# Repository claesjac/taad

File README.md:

taad
====

Tiny Autonomous Aerial Drone

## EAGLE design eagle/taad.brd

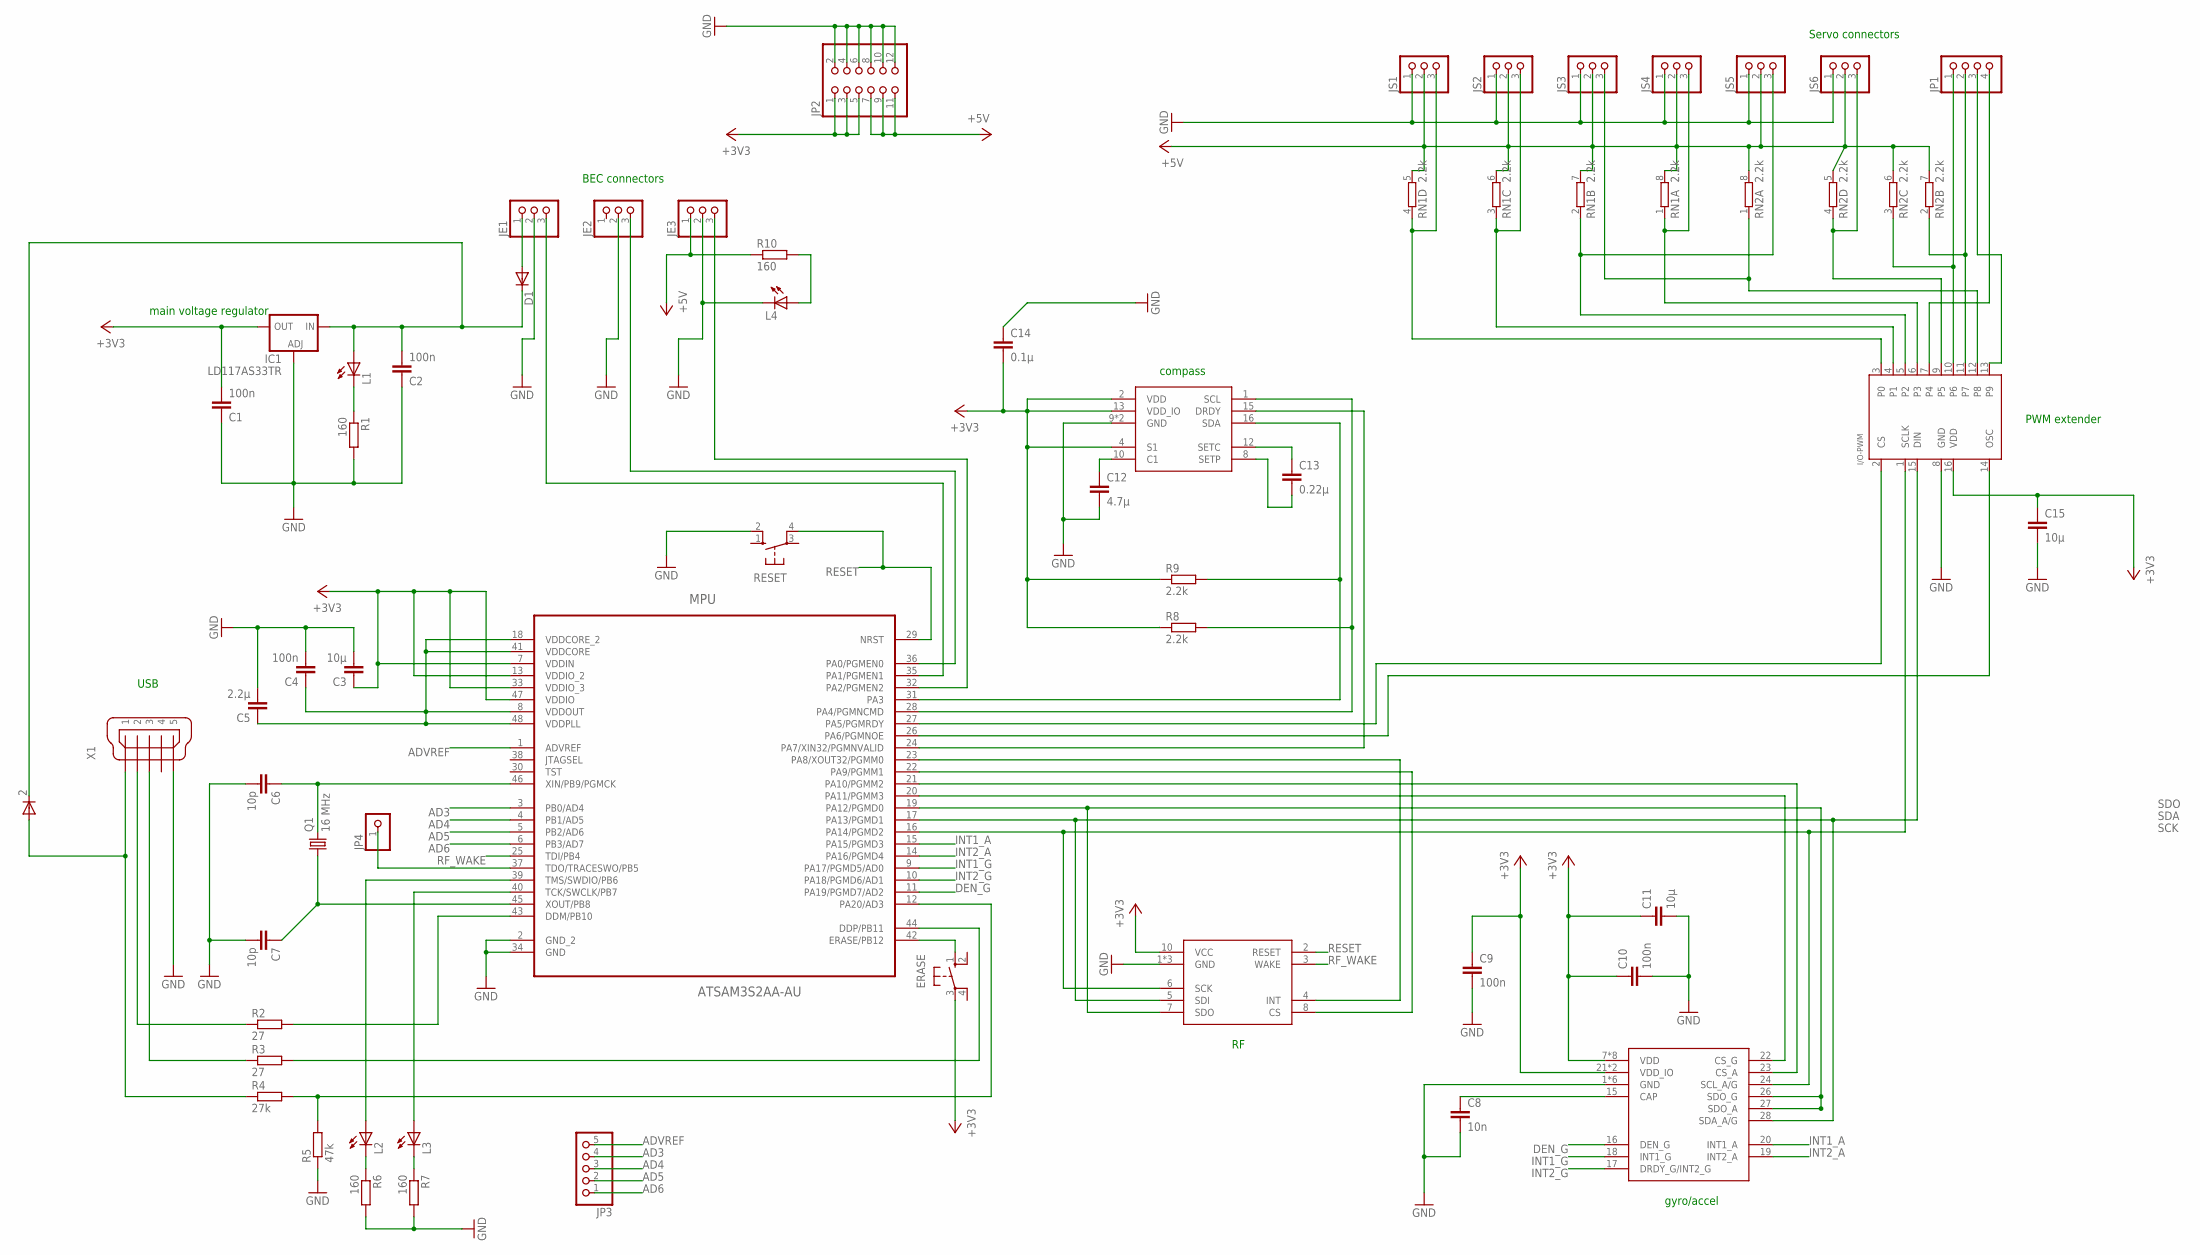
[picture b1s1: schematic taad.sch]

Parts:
2: DIODE-SOD123; SOD123
C1, C2, C4, C9, C10: 100n; C0805
C3, C11, C15: 10µ; C0805
C5: 2.2µ; C0805
C6, C7: 10p; C0805
C8: 10n; C0805
C12: 4.7µ; C0805
C13: 0.22µ; C0805
C14: 0.1µ; C0805
COMPASS: HMC5883L; LPCC16
D1: DIODE-SOD123; SOD123
ERASE: 10-XX; B3F-10XX
GYRO/ACCEL: LSM330DLC; LGA-28L
I/O-PWM: MAX6967AEE; QSOP16
IC1: LD117AS33TR; SOT223
JE1, JE2, JE3: PINHD-1X3; 1X03
JP1: PINHD-1X4; 1X04
JP2: PINHD-2X6; 2X06
JP3: PINHD-1X5; 1X05
JP4: PINHD-1X1; 1X01
JS1, JS2, JS3, JS4, JS5, JS6: PINHD-1X3; 1X03
L1, L2, L3, L4: LEDCHIP-LED0805; CHIP-LED0805
MPU: ATSAM3S2AA-AU; QFP50P900X900X160-48N
Q1: 16 MHz; HC49UP
R1, R6, R7, R10: 160; R0805
R2, R3: 27; R0805
R4: 27k; R0805
R5: 47k; R0805
R8, R9: 2.2k; R0805
RESET: 10-XX; B3F-10XX
RF: MRF24J40MA_TRANSEIVER_MODULE; PIN_HEADERS
RN1, RN2: 2.2k; EXB38V
X1: MINI-USB-32005-201; 32005-201

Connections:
+3V3: C1.2, C3.1, C9.1, C10.1, C11.1, C14.2, C15.1, COMPASS.2 (VDD), COMPASS.4 (S1), COMPASS.13 (VDD_IO), ERASE.3, GYRO/ACCEL.7 (VDD), GYRO/ACCEL.8 (VDD), GYRO/ACCEL.9 (VDD), GYRO/ACCEL.10 (VDD), GYRO/ACCEL.11 (VDD), GYRO/ACCEL.12 (VDD), GYRO/ACCEL.13 (VDD), GYRO/ACCEL.14 (VDD), GYRO/ACCEL.21 (VDD_IO), GYRO/ACCEL.25 (VDD_IO), I/O-PWM.16 (VDD), IC1.4 (OUT), JP2.1, JP2.3, JP2.5, MPU.7 (VDDIN), MPU.13 (VDDIO_2), MPU.33 (VDDIO_3), MPU.47 (VDDIO), R8.1, R9.1, RF.10 (VCC)
+5V: JE3.1, JP2.7, JP2.9, JP2.11, JS1.2, JS2.2, JS3.2, JS4.2, JS5.2, JS6.2, R10.1, RN1.5 (2), RN1.6 (2), RN1.7 (2), RN1.8 (2), RN2.5 (2), RN2.6 (2), RN2.7 (2), RN2.8 (2)
AD3: JP3.4, MPU.3 (PB0/AD4)
AD4: JP3.3, MPU.4 (PB1/AD5)
AD5: JP3.2, MPU.5 (PB2/AD6)
AD6: JP3.1, MPU.6 (PB3/AD7)
ADVREF: JP3.5, MPU.1 (ADVREF)
COMPASS_DATA_READY: COMPASS.15 (DRDY), MPU.24 (PA7/XIN32/PGMNVALID)
DDM: MPU.43 (DDM/PB10), R2.2
DDP: MPU.44 (DDP/PB11), R3.2
DEN_G: GYRO/ACCEL.16 (DEN_G), MPU.11 (PA19/PGMD7/AD2)
ESC1: JE1.3, MPU.35 (PA1/PGMEN1)
ESC2: JE2.3, MPU.36 (PA0/PGMEN0)
ESC3: JE3.3, MPU.32 (PA2/PGMEN2)
GND: C1.1, C2.1, C3.2, C4.2, C5.2, C6.2, C7.2, C8.2, C9.2, C10.2, C11.2, C12.2, C14.1, C15.2, COMPASS.9 (GND), COMPASS.11 (GND), GYRO/ACCEL.1 (GND), GYRO/ACCEL.2 (GND), GYRO/ACCEL.3 (GND), GYRO/ACCEL.4 (GND), GYRO/ACCEL.5 (GND), GYRO/ACCEL.6 (GND), I/O-PWM.8 (GND), IC1.1 (ADJ), JE1.2, JE2.2, JE3.2, JP2.2, JP2.4, JP2.6, JP2.8, JP2.10, JP2.12, JS1.1, JS2.1, JS3.1, JS4.1, JS5.1, JS6.1, L4.C, MPU.2 (GND_2), MPU.34 (GND), R1.2, R5.1, R6.2, R7.2, RESET.2 (S1), RF.1 (GND), RF.11 (GND), RF.12 (GND), X1.5
INT1_A: GYRO/ACCEL.20 (INT1_A), MPU.15 (PA15/PGMD3)
INT1_G: GYRO/ACCEL.18 (INT1_G), MPU.9 (PA17/PGMD5/AD0)
INT2_A: GYRO/ACCEL.19 (INT2_A), MPU.14 (PA16/PGMD4)
INT2_G: GYRO/ACCEL.17 (DRDY_G/INT2_G), MPU.10 (PA18/PGMD6/AD1)
IO1: I/O-PWM.10 (P6), JP1.1, RN2.3 (1)
IO2: I/O-PWM.11 (P7), JP1.2, RN2.2 (1)
IO3: I/O-PWM.13 (P9), JP1.3
IO4: I/O-PWM.7 (P4), JP1.4
unnamed: D1.A, JE1.1
unnamed: L2.A, MPU.39 (TMS/SWDIO/PB6)
unnamed: R3.1, X1.3
unnamed: R2.1, X1.2
unnamed: L1.C, R1.1
unnamed: L3.A, MPU.40 (TCK/SWCLK/PB7)
unnamed: L4.A, R10.2
unnamed: L2.C, R6.1
unnamed: L3.C, R7.1
unnamed: ERASE.1 (S), MPU.42 (ERASE/PB12)
unnamed: JP4.1, MPU.37 (TDO/TRACESWO/PB5)
unnamed: 2.C, C2.2, D1.C, IC1.3 (IN), L1.A
unnamed: C13.2, COMPASS.8 (SETP)
unnamed: C13.1, COMPASS.12 (SETC)
unnamed: C12.1, COMPASS.10 (C1)
unnamed: C8.1, GYRO/ACCEL.15 (CAP)
NPCS0: GYRO/ACCEL.22 (CS_G), MPU.20 (PA11/PGMM3)
NPCS1: MPU.22 (PA9/PGMM1), RF.8 (CS)
NPCS2: GYRO/ACCEL.23 (CS_A), MPU.21 (PA10/PGMM2)
NPCS3: I/O-PWM.2 (CS), MPU.27 (PA5/PGMRDY)
PWM_CLOCK: I/O-PWM.14 (OSC), MPU.26 (PA6/PGMNOE)
RESET: MPU.29 (NRST), RESET.4 (P1), RF.2 (RESET)
RF_INT: MPU.23 (PA8/XOUT32/PGMM0), RF.4 (INT)
RF_WAKE: MPU.25 (TDI/PB4), RF.3 (WAKE)
SCK: GYRO/ACCEL.24 (SCL_A/G), I/O-PWM.1 (SCLK), MPU.16 (PA14/PGMD2), RF.6 (SCK)
SDA: GYRO/ACCEL.28 (SDA_A/G), I/O-PWM.15 (DIN), MPU.17 (PA13/PGMD1), RF.5 (SDI)
SDO: GYRO/ACCEL.26 (SDO_G), GYRO/ACCEL.27 (SDO_A), MPU.19 (PA12/PGMD0), RF.7 (SDO)
SRV1: I/O-PWM.3 (P0), JS1.3, RN1.4 (1)
SRV2: I/O-PWM.4 (P1), JS2.3, RN1.3 (1)
SRV3: I/O-PWM.5 (P2), JS5.3, RN1.2 (1)
SRV4: I/O-PWM.6 (P3), JS4.3, RN1.1
SRV5: I/O-PWM.12 (P8), JS3.3, RN2.1
SRV6: I/O-PWM.9 (P5), JS6.3, RN2.4 (1)
TWI_CLOCK: COMPASS.1 (SCL), MPU.28 (PA4/PGMNCMD), R8.2
TWI_DATA: COMPASS.16 (SDA), MPU.31 (PA3), R9.2
USB+5V: 2.A, R4.1, X1.1
USB_CONNECTED: MPU.12 (PA20/AD3), R4.2, R5.2
VDDCORE: C4.1, C5.1, MPU.8 (VDDOUT), MPU.18 (VDDCORE_2), MPU.41 (VDDCORE), MPU.48 (VDDPLL)
XIN: C6.1, MPU.46 (XIN/PB9/PGMCK), Q1.2
XOUT: C7.1, MPU.45 (XOUT/PB8), Q1.1

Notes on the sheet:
compass
gyro/accel
PWM extender
main voltage regulator
BEC connectors
Servo connectors
USB

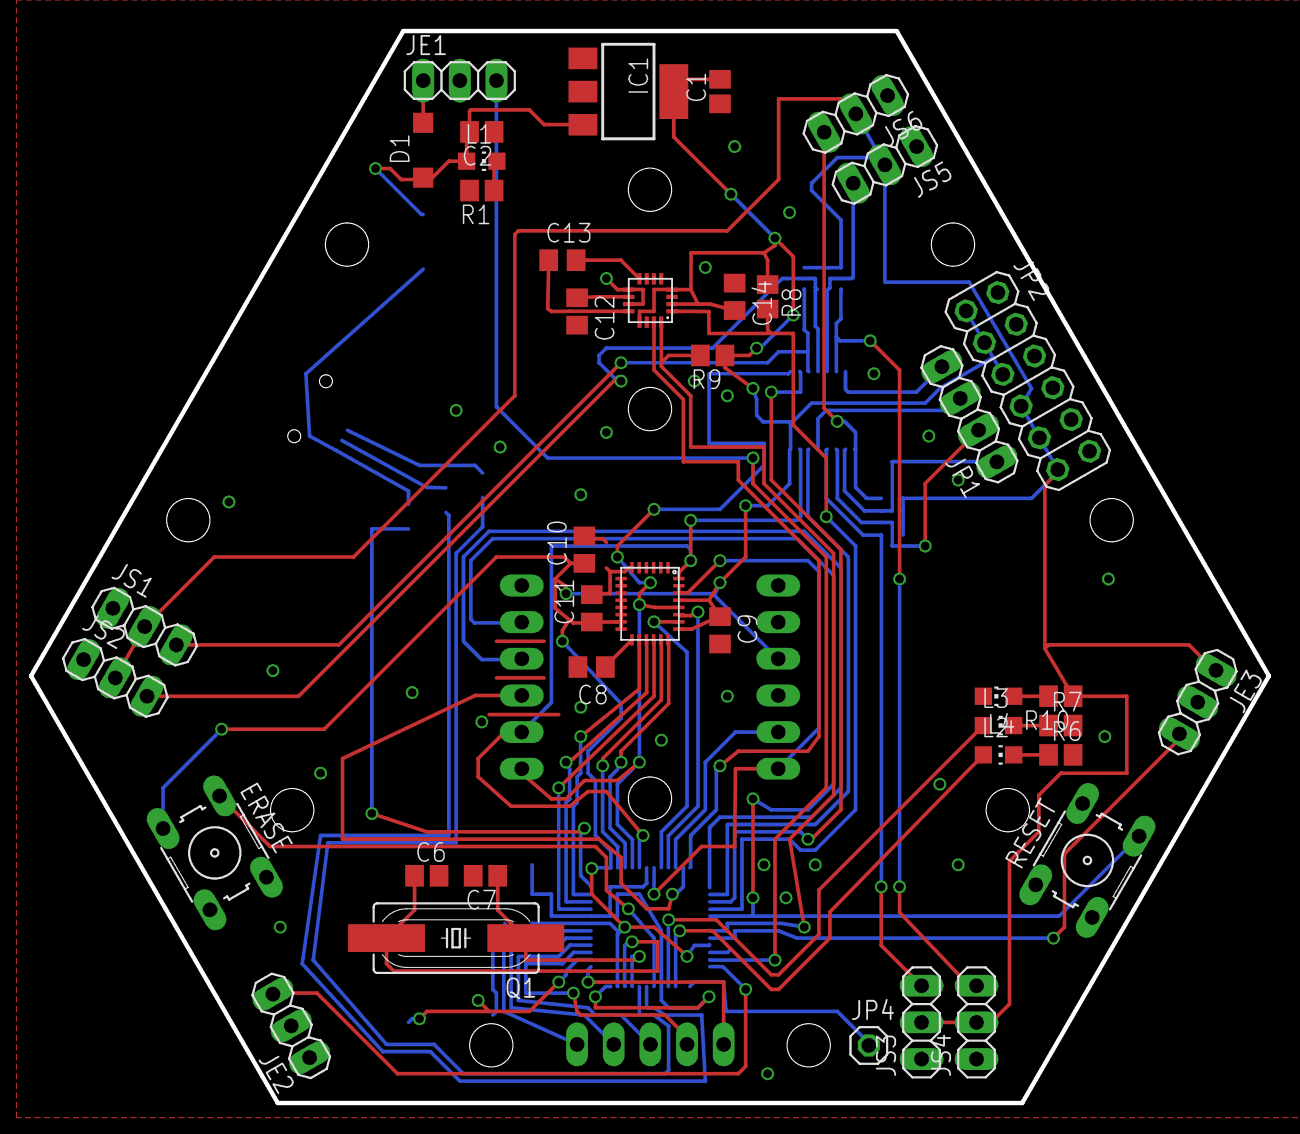
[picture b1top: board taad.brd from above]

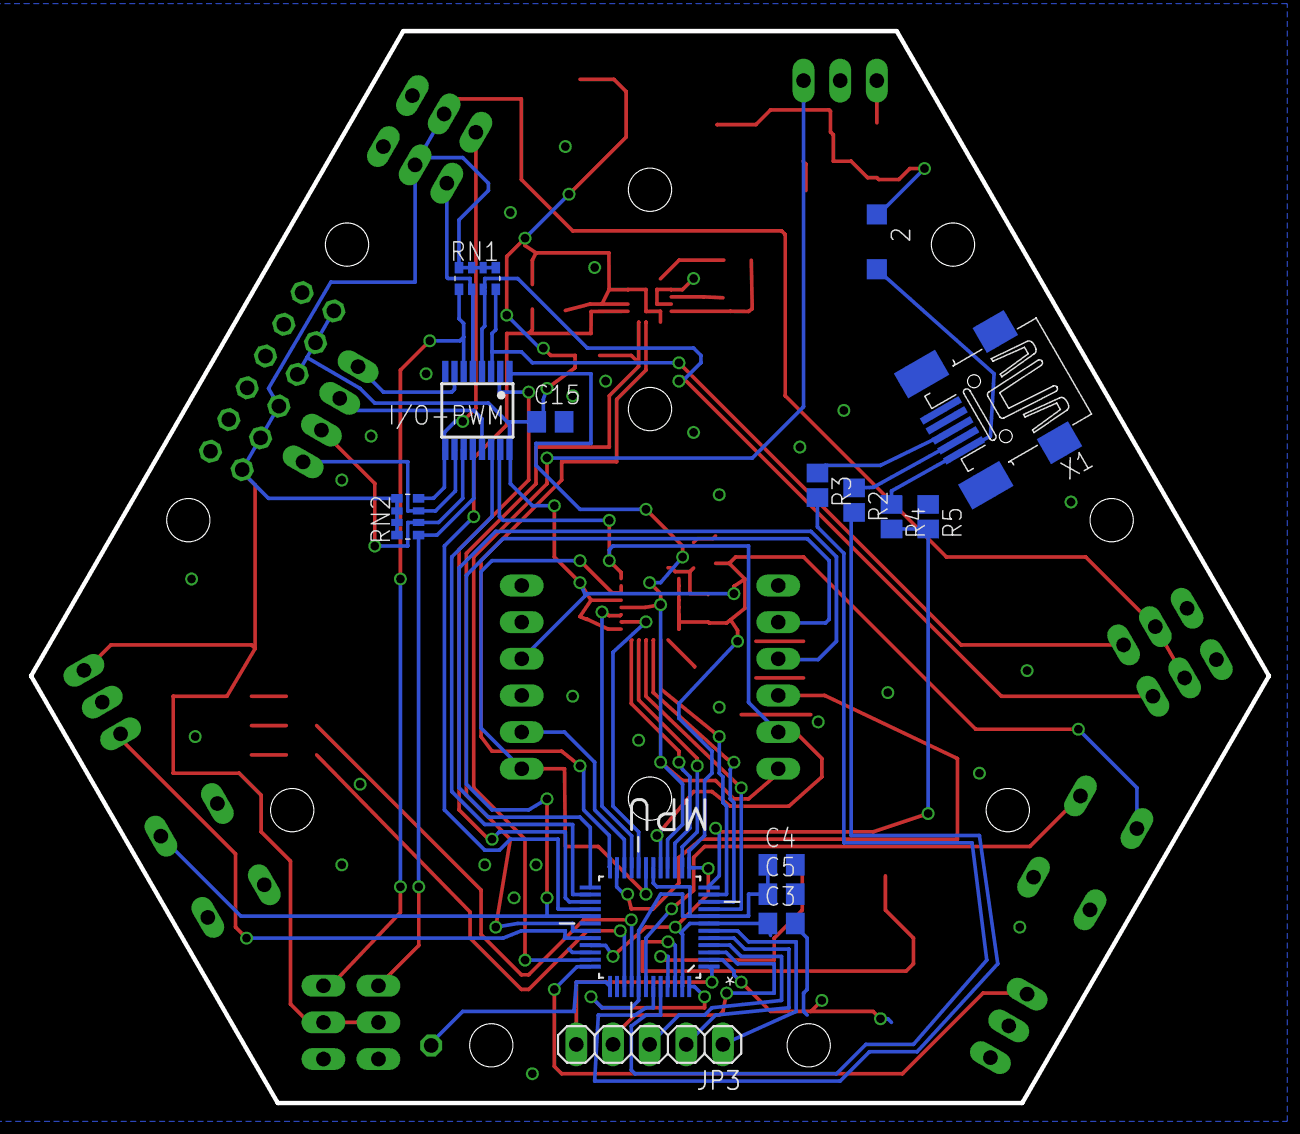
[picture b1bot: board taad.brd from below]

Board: 2 copper layers, 85.8 x 74.3 mm, 56 parts (15 on the bottom side), 63 nets.

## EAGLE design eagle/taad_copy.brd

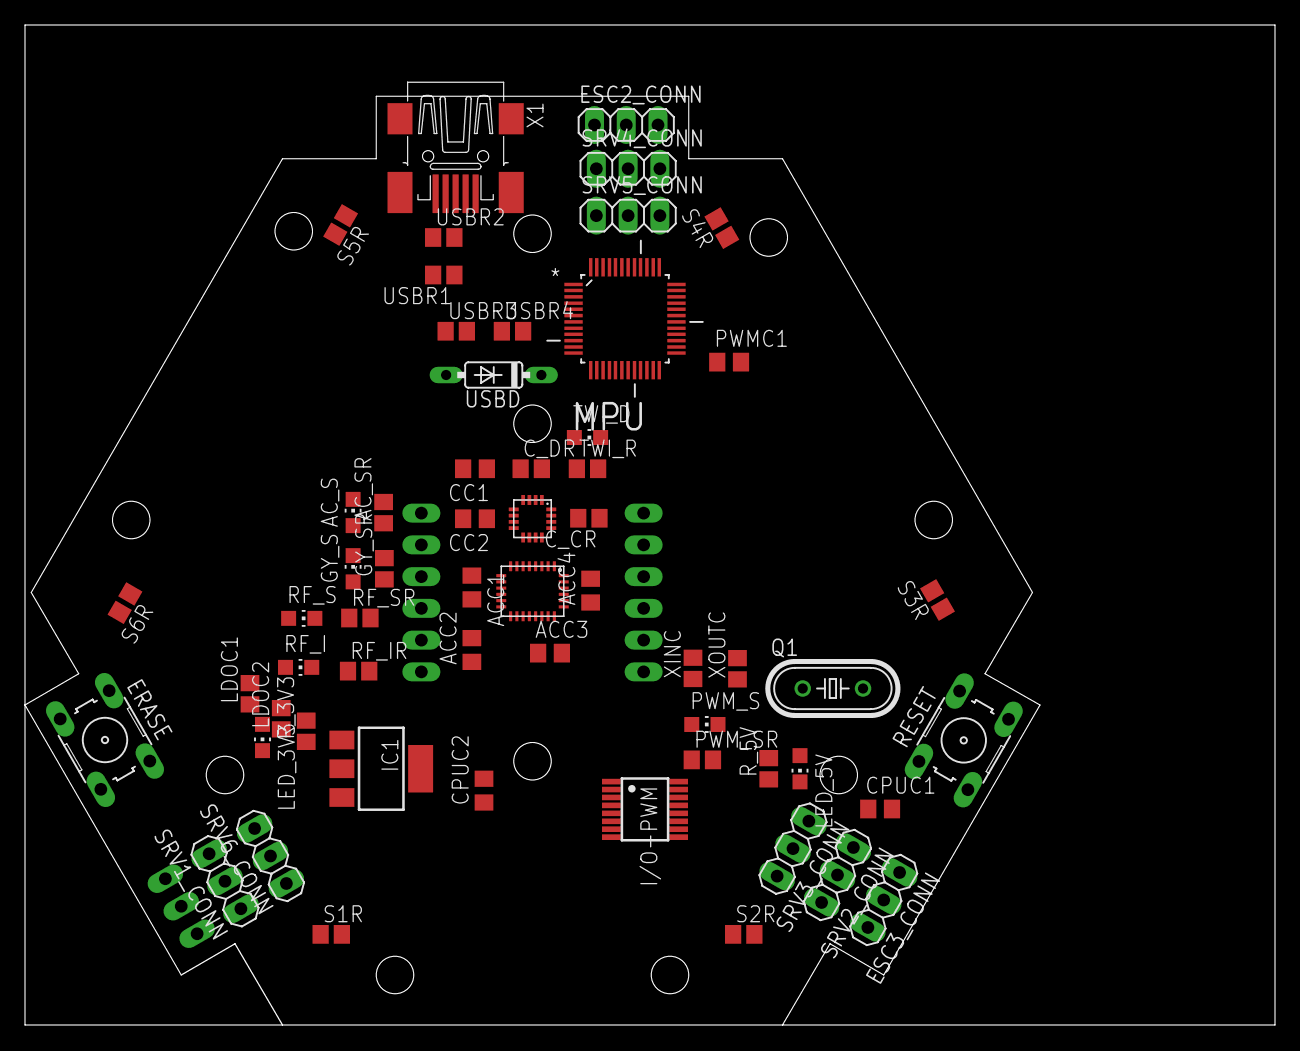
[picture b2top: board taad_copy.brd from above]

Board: 2 copper layers, 99.9 x 80.0 mm, 61 parts (1 on the bottom side), 54 nets, no tracks yet.

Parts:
ACC1, ACC3: 100n; C0805
ACC2: 10µ; C0805
ACC4: 10n; C0805
AC_S: CHIP-LED0805
AC_SR: 2.2k; R0805
CC1: 0.22µ; C0805
CC2: 4.7µ; C0805
COMPASS: HMC5883L; LPCC16
CPUC1: 2.2µ; C0805
CPUC2: 10µ; C0805
C_CR: 2.2k; R0805
C_DR: 2.2k; R0805
ERASE: B3F-10XX
ESC1_CONN, ESC2_CONN, ESC3_CONN: 1X03
GYRO/ACCEL: LSM330DLC; LGA-28L
GY_S: CHIP-LED0805
GY_SR: 2.2k; R0805
I/O-PWM: QSOP16
IC1: LD117AS33TR; SOT223
LDOC1, LDOC2: 100n; C0805
LED_3V3, LED_5V: CHIP-LED0805
MPU: ATSAM3S2AA-AU; QFP50P900X900X160-48N
PWMC1: 10µ; C0805
PWM_S: CHIP-LED0805
PWM_SR: 2.2k; R0805
Q1: 16 MHz; HC49/S
RESET: B3F-10XX
RF: MRF24J40MA_TRANSEIVER_MODULE; PIN_HEADERS
RF_I: CHIP-LED0805
RF_IR: 2.2k; R0805
RF_S: CHIP-LED0805
RF_SR: 2.2k; R0805
R_3V3, R_5V: 160; R0805
S1R, S2R, S3R, S4R, S5R, S6R: 2.2k; R0805
SRV1_CONN, SRV2_CONN, SRV3_CONN, SRV4_CONN, SRV5_CONN, SRV6_CONN: 1X03
TWI_D: CHIP-LED0805
TWI_R: 2.2k; R0805
USBD: 1N4148DO35-7; DO35-7
USBR1, USBR2: 27; R0805
USBR3: 27k; R0805
USBR4: 47k; R0805
X1: MINI-USB-32005-201; 32005-201
XINC: 10p; C0805
XOUTC: 10p; C0805

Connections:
+3V3: ACC1.1, ACC2.1, ACC3.1, COMPASS.2, COMPASS.4, COMPASS.13, CPUC2.1, C_CR.1, C_DR.1, ERASE.3, GYRO/ACCEL.7, GYRO/ACCEL.8, GYRO/ACCEL.9, GYRO/ACCEL.10, GYRO/ACCEL.11, GYRO/ACCEL.12, GYRO/ACCEL.13, GYRO/ACCEL.14, GYRO/ACCEL.21, GYRO/ACCEL.25, I/O-PWM.16, IC1.4, LDOC2.2, MPU.7, MPU.13, MPU.33, MPU.47, PWMC1.1, RF.10
+5V: ESC3_CONN.1, R_5V.1, S1R.2, S2R.2, S3R.2, S4R.2, S5R.2, S6R.2, SRV1_CONN.2, SRV2_CONN.2, SRV3_CONN.2, SRV4_CONN.2, SRV5_CONN.2, SRV6_CONN.2
DEN_G: GYRO/ACCEL.16, MPU.9
ESC1: ESC1_CONN.3, MPU.36
ESC2: ESC2_CONN.3, MPU.35
ESC3: ESC3_CONN.3, MPU.32
GND: ACC1.2, ACC2.2, ACC3.2, ACC4.2, AC_S.C, CC2.2, COMPASS.9, COMPASS.11, CPUC1.2, CPUC2.2, ESC1_CONN.2, ESC2_CONN.2, ESC3_CONN.2, GYRO/ACCEL.1, GYRO/ACCEL.2, GYRO/ACCEL.3, GYRO/ACCEL.4, GYRO/ACCEL.5, GYRO/ACCEL.6, GY_S.C, I/O-PWM.8, IC1.1, LDOC1.1, LDOC2.1, LED_3V3.C, LED_5V.C, MPU.2, MPU.34, PWM_S.C, RF.1, RF.11, RF.12, RF_I.C, RF_S.C, SRV1_CONN.1, SRV2_CONN.1, SRV3_CONN.1, SRV4_CONN.1, SRV5_CONN.1, SRV6_CONN.1, TWI_D.C, USBR4.1, X1.5, XINC.2, XOUTC.2
INT1_A: GYRO/ACCEL.20, MPU.15
INT1_G: GYRO/ACCEL.18, MPU.10
INT2_A: GYRO/ACCEL.19, MPU.14
INT2_G: GYRO/ACCEL.17, MPU.11
unnamed: MPU.46, Q1.2, XINC.1
unnamed: MPU.45, Q1.1, XOUTC.1
unnamed: USBR2.1, X1.3
unnamed: USBR1.1, X1.2
unnamed: MPU.44, USBR2.2
unnamed: LED_5V.A, R_5V.2
unnamed: CPUC1.1, MPU.8, MPU.18, MPU.41, MPU.48, RESET.3
unnamed: ERASE.1, MPU.42
unnamed: COMPASS.15, MPU.24
unnamed: I/O-PWM.6, S4R.1, SRV4_CONN.3
unnamed: I/O-PWM.14, MPU.26
unnamed: MPU.43, USBR1.2
unnamed: USBD.A, USBR3.1, X1.1
unnamed: MPU.12, USBR3.2, USBR4.2
unnamed: COMPASS.1, C_CR.2, MPU.28
unnamed: LED_3V3.A, R_3V3.2
unnamed: COMPASS.16, C_DR.2, MPU.31, TWI_R.2
unnamed: TWI_D.A, TWI_R.1
unnamed: I/O-PWM.9, S6R.1, SRV6_CONN.3
unnamed: ESC1_CONN.1, IC1.3, LDOC1.2, R_3V3.1, USBD.C
unnamed: CC1.2, COMPASS.8
unnamed: I/O-PWM.7, S5R.1, SRV5_CONN.3
unnamed: PWM_S.A, PWM_SR.1
unnamed: AC_S.A, AC_SR.1
unnamed: RF_S.A, RF_SR.1
unnamed: CC1.1, COMPASS.12
unnamed: CC2.1, COMPASS.10
unnamed: ACC4.1, GYRO/ACCEL.15
unnamed: GY_S.A, GY_SR.1
unnamed: I/O-PWM.3, S1R.1, SRV1_CONN.3
unnamed: I/O-PWM.4, S2R.1, SRV2_CONN.3
unnamed: I/O-PWM.5, S3R.1, SRV3_CONN.3
unnamed: RF_I.A, RF_IR.1
NPCS0: GYRO/ACCEL.22, GY_SR.2, MPU.20
NPCS1: MPU.22, RF.8, RF_SR.2
NPCS2: AC_SR.2, GYRO/ACCEL.23, MPU.21
NPCS3: I/O-PWM.2, MPU.27, PWM_SR.2
RESET: MPU.29, RESET.1, RF.2
RF_INT: MPU.23, RF.4, RF_IR.2
RF_WAKE: MPU.4, RF.3
SCK: GYRO/ACCEL.24, I/O-PWM.1, MPU.16, RF.6
SDA: GYRO/ACCEL.28, I/O-PWM.15, MPU.17, RF.5
SDO: GYRO/ACCEL.26, GYRO/ACCEL.27, MPU.19, RF.7

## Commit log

2012-05-11 Connecting PIN headers for engine. USB socket
2012-05-11 Added sketchup model
2012-05-12 Power regulators, LEDs that indicate power. 1x6 -> 2x3 pin headers for each pod
2012-05-13 Switched PIN header symbols and separated them into 6x3 instead of 3x6. Hooked up servo headers to power and PWM driver
2012-05-13 Replaced TLC5940 with MAX6966 as PWM servo controller
2012-05-15 Added compass
2012-05-15 New version of LSM330DLC gyro/accel
2012-05-15 Simplified schematic and made the SPI more like a bus. Updated components with new graphics and pinouts
2012-05-16 Fixed powersupply to MPU
2012-05-16 More GPIO pins connected. Fixed VCC supply issues with USB. Etc etc etc
2012-05-17 Centered origin in chip package
2012-05-18 Board
2012-05-18 Corrected package drawing since I'd drew it from bottom view
2012-05-20 Wired up everything except GND
2012-05-21 Removed
2012-05-25 Updated with recommendations from Hannes regarding capacitors on supply and some diagnostic leds. New routing of components
2012-05-26 Routed everything
2012-05-26 Increased isolation to 16mil
2012-05-28 Simplified form of PCB. Rerouted everything
2012-05-28 Route USB DDP and DDM around crystal
2012-05-28 Removed keepouts
2012-05-28 Changed 100nF to 0.1µF (same value different marking)
